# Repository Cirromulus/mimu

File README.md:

# Microphone Mute
Range Sensor for auto-muting a microphone when not in use.

## Description
On stage, noise level is high. A gate on the mics is sometimes not sufficient.
This device is intended to be mounted directly on the back of the mic, sensor facing towards mic.
The trigger-distance is adjustable by pressing the top button.
Also, by double-pressing this button, different mute-profiles will be selectable where choices can be the on- or the off-ramp time, and the dampening (gate/expander) in "mute" mode (testing required).

## BOM
Main Features:
- ATtiny88 Processor
- GY-530 IR TOF Distance Sensor (VL53L0X)
- PC817 Optocoupler as an attenuator
- AD5258 digi-potentiometer as a variable current control for the Opto

For complete list, see [BOM](pcb/mimu_phantom_bom.html)

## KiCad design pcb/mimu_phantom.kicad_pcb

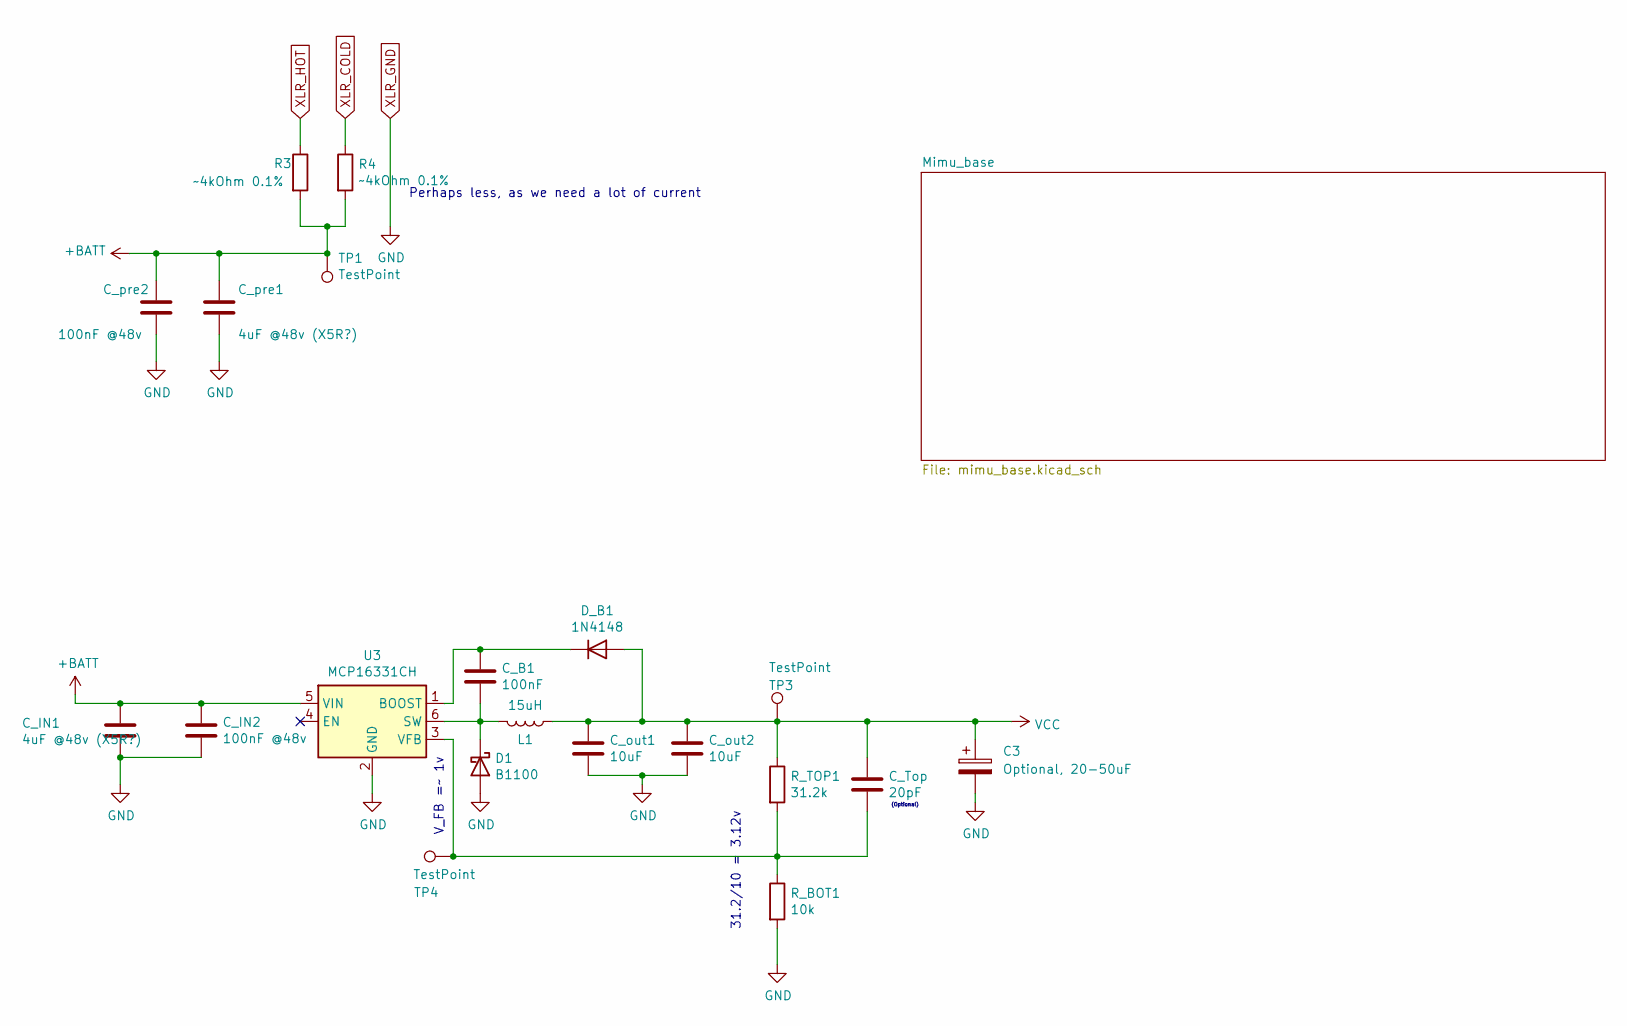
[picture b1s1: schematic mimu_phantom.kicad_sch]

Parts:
C3: Optional, 20-50uF; CP_Radial_D5.0mm_P2.00mm
C_B1: 100nF; C_1206_3216Metric_Pad1.42x1.75mm_HandSolder
C_IN1: 4uF @48v (X5R?); C_1206_3216Metric_Pad1.42x1.75mm_HandSolder
C_IN2: 100nF @48v; C_1206_3216Metric_Pad1.42x1.75mm_HandSolder
C_Top: 20pF; C_1206_3216Metric_Pad1.42x1.75mm_HandSolder
C_out1, C_out2: 10uF; C_1206_3216Metric_Pad1.42x1.75mm_HandSolder
C_pre1: 4uF @48v (X5R?); C_1206_3216Metric_Pad1.33x1.80mm_HandSolder
C_pre2: 100nF @48v; C_1206_3216Metric_Pad1.33x1.80mm_HandSolder
D1: B1100; D_SMA
D_B1: 1N4148; D_SOD-323_HandSoldering
L1: 15uH; L_7.3x7.3_H4.5
R3, R4: ~4kOhm 0.1%; R_1206_3216Metric_Pad1.30x1.75mm_HandSolder
R_BOT1: 10k; R_1206_3216Metric_Pad1.42x1.75mm_HandSolder
R_TOP1: 31.2k; R_1206_3216Metric_Pad1.42x1.75mm_HandSolder
TP1, TP3, TP4: TestPoint; Measurement_Point_Round-SMD-Pad_Small
U3: MCP16331CH; SOT-23-6

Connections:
+BATT: C_IN1.1, C_IN2.1, C_pre1.1, C_pre2.1, R3.2, R4.2, TP1.1, U3.5 (VIN)
unnamed: C_B1.2, D1.1 (K), L1.2, U3.6 (SW)
unnamed: C_B1.1, D_B1.1 (K), U3.1 (BOOST)
unnamed: C_Top.2, R_BOT1.1, R_TOP1.2, TP4.1, U3.3 (VFB)
VCC: C3.1, C_Top.1, C_out1.1, C_out2.1, D_B1.2 (A), L1.1, R_TOP1.1, TP3.1; also elsewhere on the board
XLR_COLD: R4.1; also elsewhere on the board
XLR_GND: C3.2, C_IN1.2, C_IN2.2, C_out1.2, C_out2.2, C_pre1.2, C_pre2.2, D1.2 (A), R_BOT1.2, U3.2 (GND); also elsewhere on the board
XLR_HOT: R3.1; also elsewhere on the board

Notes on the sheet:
31.2/10 = 3.12v
Perhaps less, as we need a lot of current
V_FB =~ 1v
(Optional)

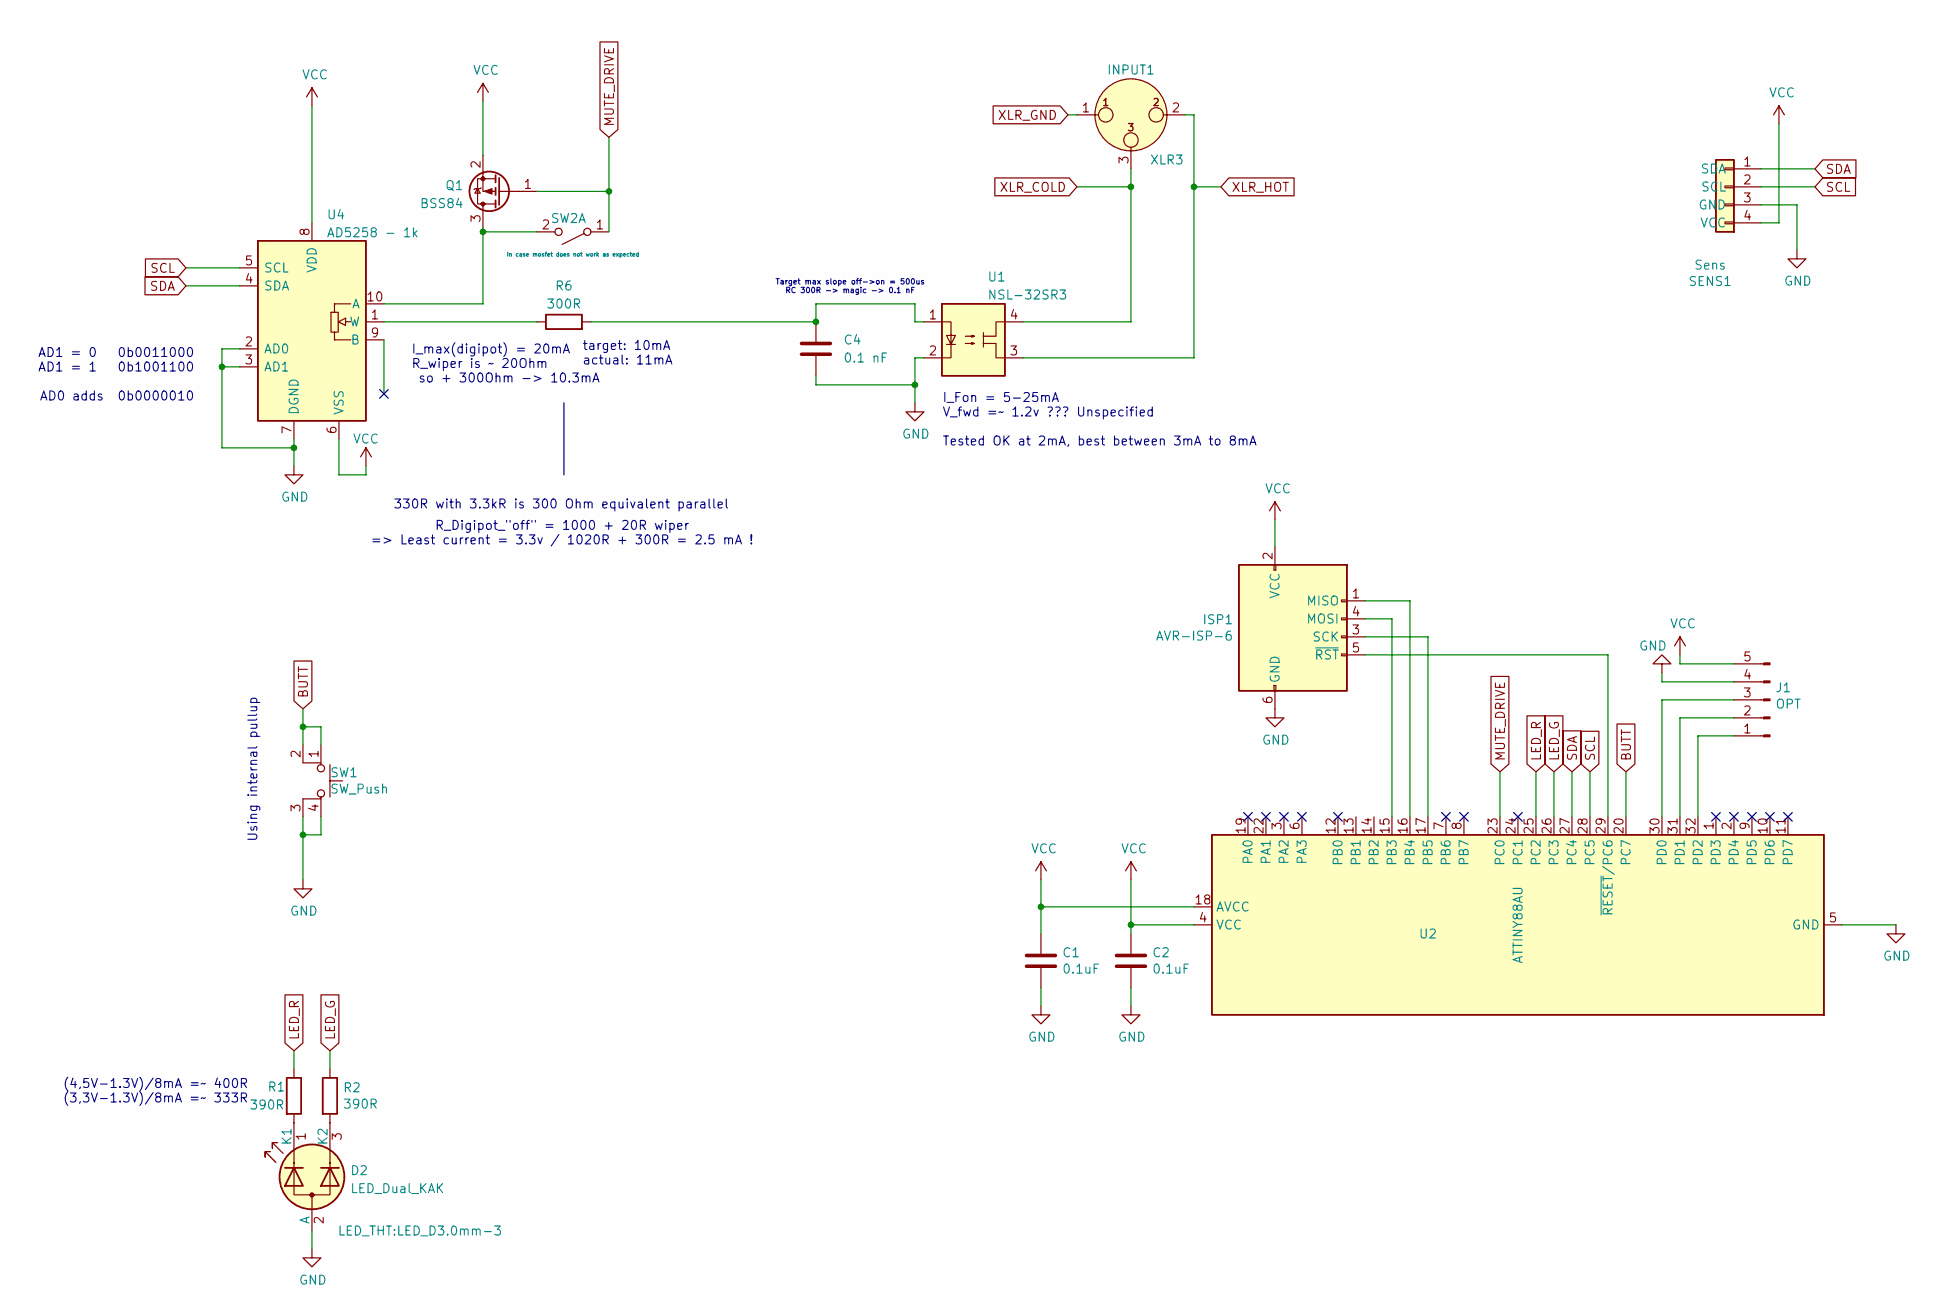
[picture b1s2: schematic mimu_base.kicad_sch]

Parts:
C1, C2: 0.1uF; C_1206_3216Metric_Pad1.33x1.80mm_HandSolder
C4: 0.1 nF; R_1206_3216Metric_Pad1.30x1.75mm_HandSolder
D2: LED_Dual_KAK; LED_D3.0mm-3
INPUT1: XLR3; PinHeader_1x03_P2.54mm_Vertical
ISP1: AVR-ISP-6; PinHeader_2x03_P2.54mm_Vertical_pogo
J1: OPT; PinHeader_1x05_P1.27mm_Vertical
Q1: BSS84; SOT-23
R1: 390R; C_1206_3216Metric_Pad1.33x1.80mm_HandSolder
R2: 390R; R_1206_3216Metric_Pad1.30x1.75mm_HandSolder
R6: 300R; R_1206_3216Metric_Pad1.30x1.75mm_HandSolder
SENS1: Sens; PinHeader_1x04_P2.54mm_Vertical
SW1: SW_Push; Switch_Tactile_SMD_6x6mm_PTS645
SW2: In case mosfet does not work as expected; SolderJumper-2_P1.3mm_Open_TrianglePad1.0x1.5mm
U1: NSL-32SR3; DIP-4_bubble_W7.62mm
U2: ATTINY88AU; TQFP-32_7x7mm_P0.8mm
U4: AD5258 - 1k; MSOP-10_3x3mm_P0.5mm

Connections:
BUTT: SW1.1, SW1.2, U2.20 (PC7)
LED_G: R2.1, U2.26 (PC3)
LED_R: R1.1, U2.25 (PC2)
MUTE_DRIVE: Q1.1 (G), SW2.1 (A), U2.23 (PC0)
unnamed: C4.1, R6.2, U1.1
unnamed: D2.1 (K1), R1.2
unnamed: D2.3 (K2), R2.2
unnamed: ISP1.1 (MISO), U2.16 (PB4)
unnamed: ISP1.4 (MOSI), U2.15 (PB3)
unnamed: ISP1.3 (SCK), U2.17 (PB5)
unnamed: ISP1.5 (~RST), U2.29 (~RESET/PC6)
unnamed: J1.1, U2.32 (PD2)
unnamed: J1.2, U2.31 (PD1)
unnamed: J1.3, U2.30 (PD0)
unnamed: Q1.3 (D), SW2.2 (B), U4.10 (A)
unnamed: R6.1, U4.1 (W)
SCL: SENS1.2 (SCL), U2.28 (PC5), U4.5 (SCL)
SDA: SENS1.1 (SDA), U2.27 (PC4), U4.4 (SDA)
VCC: C1.1, C2.1, ISP1.2 (VCC), J1.5, Q1.2 (S), SENS1.4 (VCC), U2.4 (VCC), U2.18 (AVCC), U4.6 (VSS), U4.8 (VDD); also elsewhere on the board
XLR_COLD: INPUT1.3, U1.4; also elsewhere on the board
XLR_GND: C1.2, C2.2, C4.2, D2.2 (A), INPUT1.1, ISP1.6 (GND), J1.4, SENS1.3 (GND), SW1.3 (K), SW1.4 (A), U1.2, U2.5 (GND), U2.21 (GND), U4.2 (AD0), U4.3 (AD1), U4.7 (DGND); also elsewhere on the board
XLR_HOT: INPUT1.2, U1.3; also elsewhere on the board

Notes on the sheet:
Using internal pullup
R_Digipot_"off" = 1000 + 20R wiper => Least current = 3.3v / 1020R + 300R = 2.5 mA !
330R with 3.3kR is 300 Ohm equivalent parallel
I_max(digipot) = 20mA R_wiper is ~ 20Ohm so + 300Ohm -> 10.3mA
I_Fon = 5-25mA V_fwd =~ 1.2v ??? Unspecified Tested OK at 2mA, best between 3mA to 8mA
AD1 = 0 0b0011000 AD1 = 1 0b1001100 AD0 adds 0b0000010
target: 10mA actual: 11mA
(4,5V-1.3V)/8mA =~ 400R (3,3V-1.3V)/8mA =~ 333R
Target max slope off->on = 500us RC 300R -> magic -> 0.1 nF

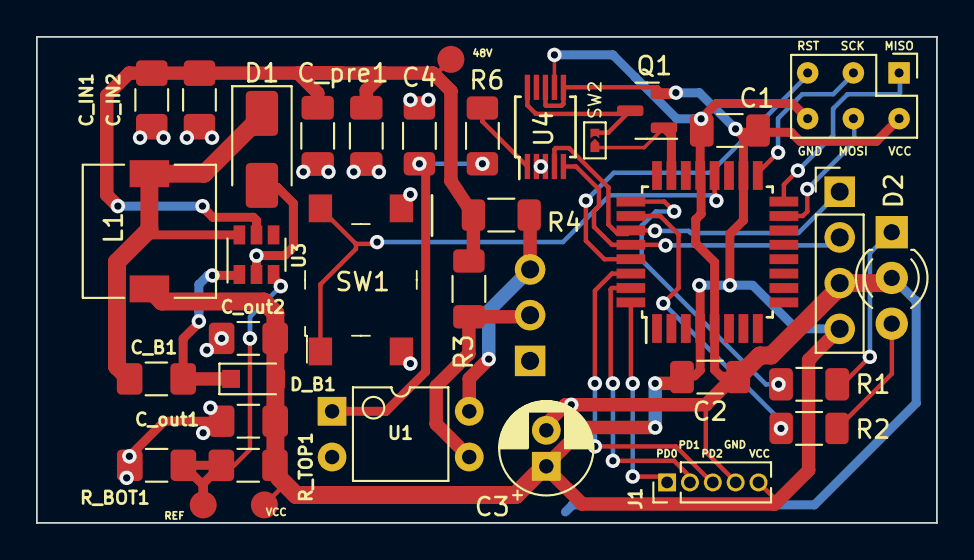
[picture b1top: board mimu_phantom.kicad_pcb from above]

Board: 2 copper layers, 50.0 x 27.0 mm, 36 parts (1 on the bottom side), 26 nets.

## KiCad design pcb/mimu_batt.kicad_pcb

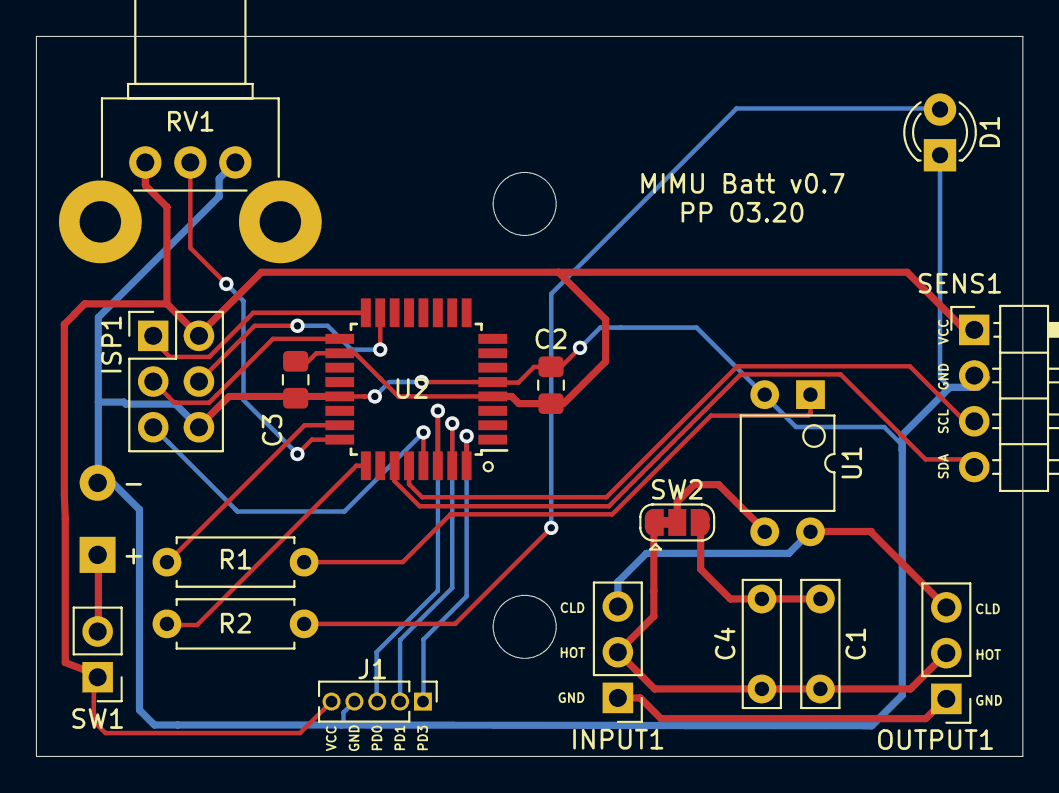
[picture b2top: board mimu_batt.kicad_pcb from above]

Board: 2 copper layers, 54.8 x 40.0 mm, 18 parts (1 on the bottom side), 22 nets.

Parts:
BT1: 4.5V; BatteryHolder_Generic_3xAAA
C1, C4: 1uF; C_Rect_L7.0mm_W2.0mm_P5.00mm
C2, C3: 0.1uF; C_0805_2012Metric_Pad1.15x1.40mm_HandSolder
D1: LED; LED_D3.0mm
INPUT1: XLR3; PinHeader_1x03_P2.54mm_Vertical
ISP1: AVR-ISP-6; PinHeader_2x03_P2.54mm_Vertical
J1: OPT; PinHeader_1x05_P1.27mm_Vertical
OUTPUT1: XLR3; PinHeader_1x03_P2.54mm_Vertical
R1: 110R; R_Axial_DIN0207_L6.3mm_D2.5mm_P7.62mm_Horizontal
R2: 165R; R_Axial_DIN0207_L6.3mm_D2.5mm_P7.62mm_Horizontal
RV1: 1K_POT; Potentiometer_Bourns_PTV09A-2_Vertical
SENS1: Sens; PinHeader_1x04_P2.54mm_Horizontal
SW1: ONOFF; Pin_Header_Straight_1x02_Pitch2.54mm
SW2: SW_DPDT_x2; SolderJumper-3_P1.3mm_Bridged12_RoundedPad1.0x1.5mm
U1: AQY211EH; DIP-4_bubble_W7.62mm
U2: ATTINY88AU; TQFP-32_7x7mm_P0.8mm

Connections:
+3V0: C2.1, C3.1, ISP1.2, J1.5, RV1.3, SENS1.1, U2.4, U2.18
GND: BT1.2, C2.2, C3.2, D1.1, ISP1.6, J1.4, RV1.1, SENS1.2, U1.2, U2.5, U2.21
LED: R2.1, U2.25
MUTE: R1.1, U2.23
unnamed: BT1.1, SW1.2
unnamed: C1.1, C4.1, INPUT1.2, OUTPUT1.2, SW2.1
unnamed: C1.2, C4.2, SW2.3
unnamed: D1.2, R2.2
unnamed: INPUT1.1, OUTPUT1.1
unnamed: INPUT1.3, OUTPUT1.3, U1.4
unnamed: ISP1.1, U2.16
unnamed: ISP1.3, U2.17
unnamed: ISP1.4, U2.15
unnamed: ISP1.5, U2.29
unnamed: J1.1, U2.32
unnamed: J1.2, U2.31
unnamed: J1.3, U2.30
unnamed: R1.2, U1.1
unnamed: SW2.2, U1.3
POT: RV1.2, U2.24
SCL: SENS1.3, U2.28
SDA: SENS1.4, U2.27

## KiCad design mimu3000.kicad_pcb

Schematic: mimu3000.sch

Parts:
BT1: 3V; BatteryHolder_Keystone_2468_2xAAA
C1: 47µ; CP_Radial_D5.0mm_P2.50mm
D1: LED; LED_D3.0mm
INPUT1: XLR3; PinHeader_1x03_P2.54mm_Vertical
ISP1: AVR-ISP-6; PinHeader_2x03_P2.54mm_Vertical
OUTPUT1: XLR3; PinHeader_1x03_P2.54mm_Vertical
R1: 100R; R_Axial_DIN0207_L6.3mm_D2.5mm_P7.62mm_Horizontal
R2: 90R; R_Axial_DIN0207_L6.3mm_D2.5mm_P7.62mm_Horizontal
RV1: R_POT; Potentiometer_Alps_RK09Y11_Single_Horizontal
SENS1: Sens; PinHeader_1x04_P2.54mm_Vertical
SW1: P_MISO; PinHeader_1x03_P2.54mm_Vertical
SW2: P_MOSI; PinHeader_1x03_P2.54mm_Vertical
U1: ATTINY13A-SSU; SOIC-8_3.9x4.9mm_P1.27mm
U2: AQY211EH; DIP-4_W7.62mm

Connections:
unnamed: BT1.1 (+), ISP1.2 (VCC), RV1.1, SENS1.1, U1.8 (VCC)
unnamed: BT1.2 (-), D1.1 (K), ISP1.6 (GND), RV1.3, SENS1.2, U1.4 (GND), U2.2
unnamed: C1.1, R1.2
unnamed: C1.2, U2.1
unnamed: D1.2 (A), R2.2
unnamed: INPUT1.1, OUTPUT1.1
unnamed: INPUT1.2, OUTPUT1.2, U2.3
unnamed: INPUT1.3, OUTPUT1.3, U2.4
unnamed: ISP1.1 (MISO), SW1.1 (A)
unnamed: ISP1.3 (SCK), SENS1.4, U1.7 (PB2(SCK/ADC1/T0/PCINT2))
unnamed: ISP1.4 (MOSI), SW2.1 (A)
unnamed: ISP1.5 (~RST), U1.1 (PB5(~RESET~/ADC0/PCINT5/dW))
unnamed: R1.1, SW2.3 (C)
unnamed: R2.1, SW1.3 (C)
unnamed: RV1.2, U1.3 (PB4(ADC2/PCINT4))
unnamed: SENS1.3, U1.2 (PB3(CLKI/ADC3/PCINT3))
unnamed: SW1.2 (B), U1.6 (PB1(MISO/AIN1/OC0B/INT0/PCINT1))
unnamed: SW2.2 (B), U1.5 (PB0(MOSI/AIN0/OC0A/PCINT0))

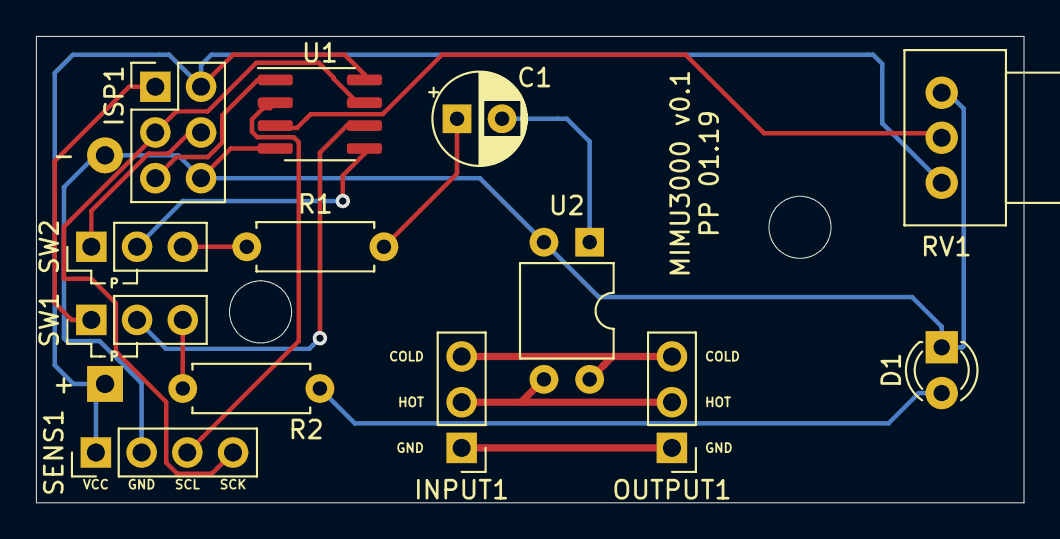
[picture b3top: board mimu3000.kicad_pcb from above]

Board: 2 copper layers, 54.9 x 25.9 mm, 14 parts (1 on the bottom side), 18 nets.

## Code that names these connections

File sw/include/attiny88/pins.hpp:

#include <inttypes.h>
#include <Arduino.h>

static constexpr uint8_t MUTE_DRIVE = 17;   //PC0
static constexpr uint8_t BUTTON     = 16;   //PC7
static constexpr uint8_t LEDG       = 19;   //PC2
static constexpr uint8_t LEDR       = 20;   //PC3
static constexpr uint8_t J0   = 0;
static constexpr uint8_t J1   = 1;
static constexpr uint8_t J2   = 2;

static constexpr bool has_serial = false;

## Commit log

2020-02-04 added 3d render of pcb
2020-02-04 added Optocoupler spec sheet
2020-02-04 Updated to using new low R_on optocoupler
2020-02-04 Fixed courtyard
2020-02-04 Added jumper for demo
2020-02-05 added BOM
2020-02-05 Description describes
2020-02-05 Initial Test for soft I2C
2020-02-05 Soft I2C uses 3.7 times the available progmem.
2020-02-06 Switched to attiny48
2020-02-06 Now using attiny48 (88 for memory analysis, PIO sucks)
2020-02-07 Capacitance needed?
2020-02-07 Still too much progmem
2020-02-07 We have to use Attiny88
2020-02-07 Added 3 extra IO
2020-02-10 Use realworld-potentiometer
2020-02-10 something
2020-02-10 added Batt_low warning
2020-02-11 Switched to 3xAAA container, Vertically fixed Sensor and the possibility to adding a tantal for de-pop
2020-02-11 added JCL number placeholder
2020-02-12 pcb/gerber/
2020-02-12 refs updated
2020-02-12 What?
2020-02-12 Referenced BOM
2020-02-17 Missed something
2020-02-17 Use electrolyte caps
2020-02-18 Flipped Sensor to save space
2020-02-18 Added example LDO for future phantom power usage
2020-02-18 Gerber files of Version 0.4
2020-02-18 Added placeholder for case
2020-03-09 Fixed wrong-sized pitch of sensor, corrected witdh of a track. easier footprint for opto
2020-03-10 Fixed misconception that a Capacitor before Opto would smooth the curve
2020-03-12 divided schematics to hierarchically have battery and phantom powered variant
2020-03-12 I hope this did not break everything
2020-03-13 Quick layout test
2020-03-14 Now it just has to work, lol
2020-03-17 Dey see me layoutin', dey hatin'
2020-03-17 Buy all the shit
2020-03-26 Timeouting :(
2020-03-26 Argh, forgot wire.begin!!!!!!
2020-03-26 Works this way!
2020-03-26 Now including Potentiometer readout
2020-03-26 Wow, the internal voltage reference actually works!
2020-03-26 Increased Warning Voltage And fixed bug in warning blink
2020-03-26 Resistor Values now Reality-proven
2020-03-27 Bump near-final version for battery powered version. Todo: Maybe remove the capacitor? Needs realworld-test.
2020-03-27 Quick order of some pcbs
2020-03-27 Better blinking.
2020-04-14 Batch 2
2020-04-14 Batch 1
2020-04-14 Cap not needed for XLR
2020-04-15 Added an "always off" range to the Poti
2020-04-15 Pushing it to the limit
2020-09-04 added first iteration of STLs for vertical MiMuBat case
2020-09-04 updated some play dimensions for better fit
2020-09-04 optimized wall thicknesses for 3d print
2020-09-06 Added 3d-Renderings of the PCB
2020-09-07 updated geometry. Case now allows actual placement of battery holder. Additional bug fixes and performance. Better camera.
2020-09-07 added stl files with higher res
2020-09-07 removed step files
2020-09-07 cleanup
2020-09-08 Ok, STL then.
2020-09-09 updated todo.md
2020-09-10 improved V1, fixed tolerances, changed tof Window to 2 seperate holes, broadened lock mech. of lid, fixed batt freeplay, reduced pocket for Tof and cabling, moved output conn back for easier assembly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
2020-09-11 fixed problem with lid locking mechanism and optimized tof window width
2020-09-11 Delete lockfile.lck
    This is not relevant in this Repo
2020-09-11 Create LICENSE
2020-09-19 Decrease timing budget. Is this still ok?
2020-09-19 added stls for case with internal xlr male jack instead of clr plug
2020-09-20 Use "debug" pins
2020-09-23 updated stls for case with xlr socket now also fits in the lid.Also increased play of bat holder and moved tof window down .8mm
2020-09-29 Further decrease Latency
2020-10-04 optimized tolerances of XLR jack geometry
2020-10-06 optimized case and lid depth for XLR jack variant. Also bug fixes and improvements, better camera and stability.
2020-10-24 Use own fork
2020-10-24 set measurement budget according to min
2020-10-24 le buidl
2020-10-24 Use own registered library
2020-10-24 Added Debounce
2020-10-24 Added datasheet
2020-10-24 Stopped using Timer0 used by millis(), also added timeout. Fixes #4.
2021-08-17 Added original Library to compare
2021-08-17 Something new about the PCB?
2021-08-17 This confirms that the problem is caused by to little memory
2021-08-17 Removed obsolete render
2021-08-17 Made Shutdown mute state configurable, increased timeout duration to 2hrs
2021-08-30 Fixed wrong timer calculation and reduced delay&energy consumption with forgotten batt_check reset
2021-08-30 new rendering?
2021-09-09 better configurability
2021-09-09 Sensor communication timeout now calculated
2021-09-09 Added deadzone and filtering (filter is too slow)
2021-09-09 Using bug-fixed version, now timing budget can be reduced immensely
2021-09-13 Optimizing battery check away on new mimu phantom target
2021-09-13 More resiliency
2021-09-16 Remove idle timeout in phantom powered mimu
2021-09-21 Increase min Limunosity && Cleanup
2021-10-14 Looking into fading/padding
2021-10-15 Easy Library, but i did blow up the chip (lol)
2021-10-17 This might actually work
2021-10-18 Connected Attenuation to PWM-Able pin
2021-10-18 Updated new BOM file name
2021-10-18 Re-Render for good measure.
2021-10-24 Bugfix: Added missing filter cap on PWM output
2021-10-25 Forgot exporting BOM
2022-11-10 Deciding which 'soft' optocouple to use
2022-11-20 re-structured 3D-Models so that scaling is correct
2022-12-17 First working version of Digipot
2022-12-17 Additional drive pin _must_ use pnp transistor
2022-12-18 First draft of ad5258 lib
2022-12-19 First impression of AD5258 lib
2022-12-19 Dropped support for battery handling
2022-12-19 Introduced the notion of a MuteProfile
2022-12-19 Further cleanup.
2022-12-20 First impression of new v3!
2022-12-20 First layout
2022-12-21 Minor PCB updates
2022-12-21 Exported renderings
2022-12-22 Added Switch for drive_fallback mode
2022-12-22 Dropped support for mimu_batt
2022-12-22 Exported gerber files as zip
2022-12-22 Fixed Issue #6 by mirroring TOF connector pins
2023-01-03 Smaller fab text for printing cheat-sheet
2023-01-08 Fixed pin numbers
2023-01-10 Crash at sensor.init()
2023-01-10 Enabled O2 optimizations: Mainly funcion inlining. This way, it is actually able to use the sensor
2023-01-10 With small Wire lib and original pololu lib it seems to accurately measure things
2023-01-11 framework-arduino-avr-attiny needs patching if less RAM is desired
2023-01-12 Made patch applyable.
    With this patch for *Wire*, the difference in RAM usage is huge:
    Previously:
    ```
    RAM: [=== ] 31.6% (used 162 bytes from 512 bytes)
    Flash: [========= ] 90.6% (used 7422 bytes from 8192 bytes)
    ```
2023-01-12 separated mutehandling header from implementation
2023-01-12 Added static_print, corrected assumption
2023-01-13 Fixed digipot value calculation
2023-01-13 Improved Error handling and signalling
2023-01-13 Fixed Overflow with large/ish fade times
2023-01-14 Fixed bug of debounceing causing oscillations
2023-01-14 Allowed for occasional sensor timeouts. But why do they happen?
    Happens occasionally when switching between infinity and measureable, or inf. and switch?
2023-01-27 Removed some Debug writes
2024-01-21 Test with using the other optocoupler that needs less current
2024-01-21 Corrected spelling mistake
2024-04-06 Added wait before accessing tof sensor
2024-04-06 Initial playarounds for rheostat mode
2024-04-06 Small cleanups
2024-04-07 Some goof-arounds, but real prototype still produces wobbles with sensor current draw
2024-04-13 Added emphasis on having less VCC. 3v work fine, perhaps even less.
2026-06-07 Wait for user input on button-press on startup
2026-06-30 Initial build with eeprom
2026-06-30 Now actually only saving if button was released (perhaps_
2026-06-30 Actually storing it in EEPROM, upsi
2026-06-30 Less delay (but more powerdraw)
2026-06-30 Added a little "success" blink on distance save
